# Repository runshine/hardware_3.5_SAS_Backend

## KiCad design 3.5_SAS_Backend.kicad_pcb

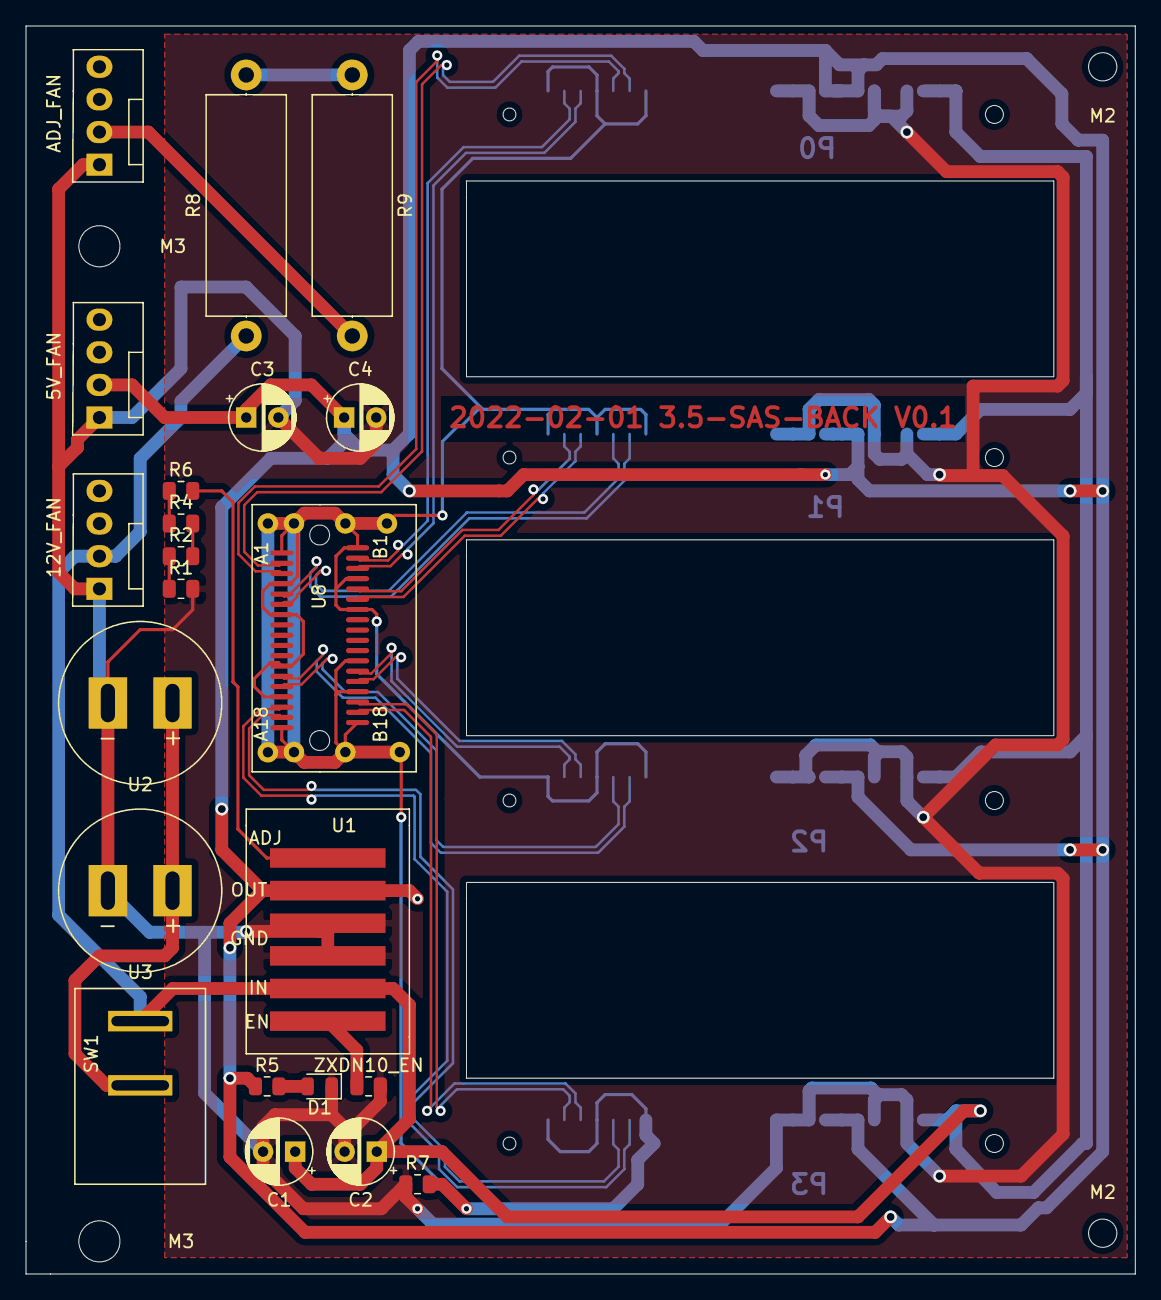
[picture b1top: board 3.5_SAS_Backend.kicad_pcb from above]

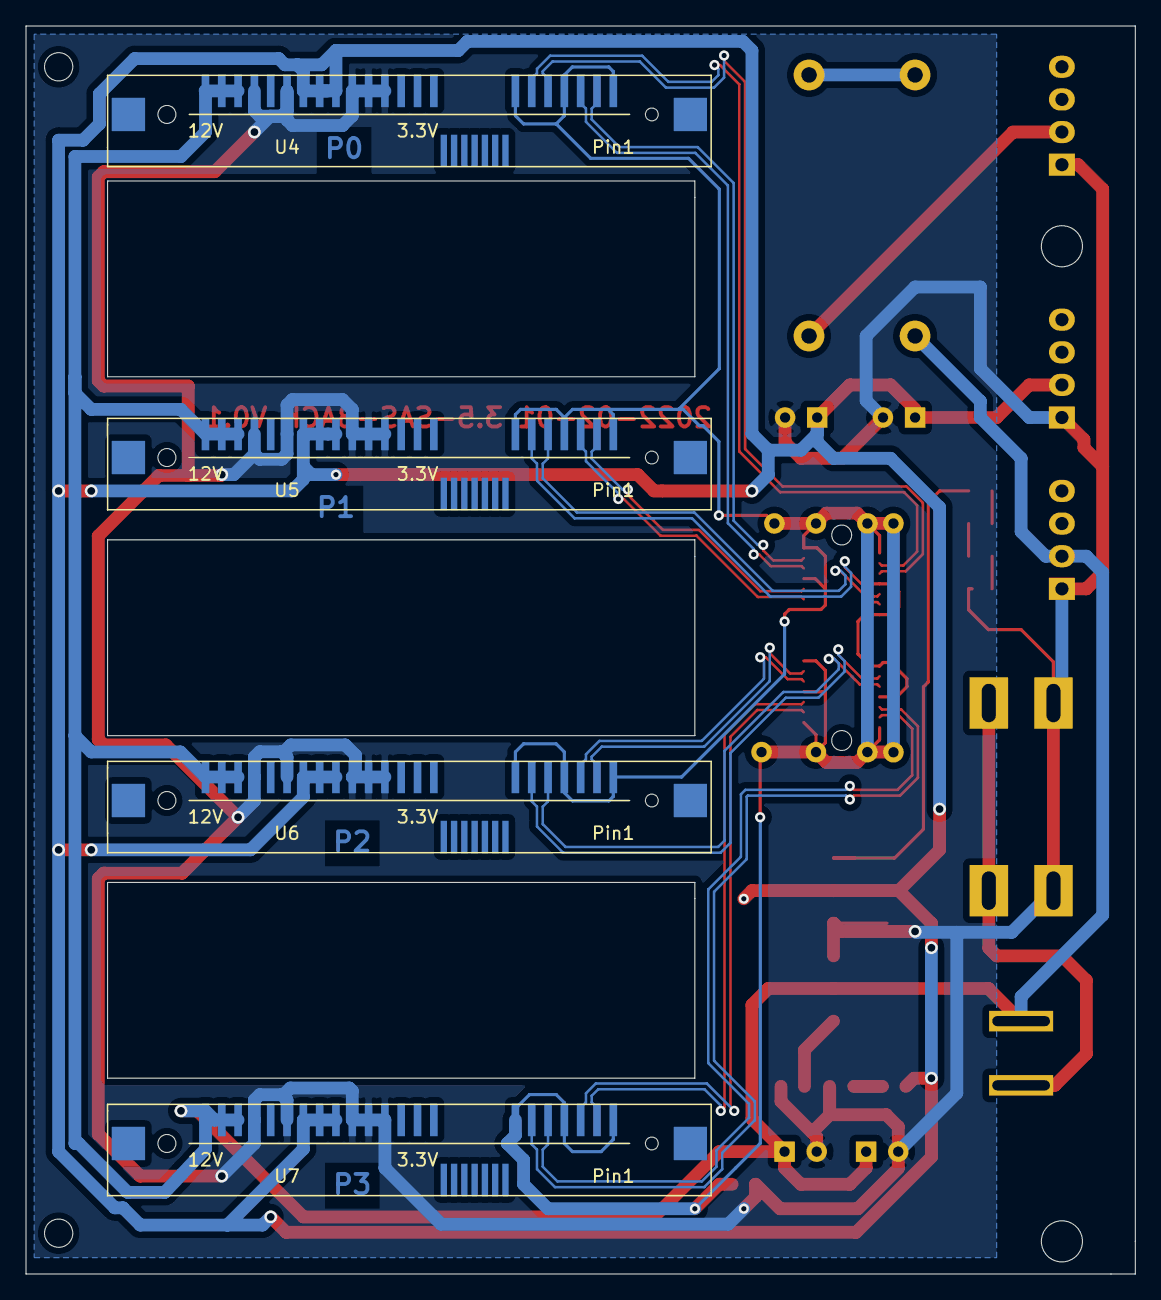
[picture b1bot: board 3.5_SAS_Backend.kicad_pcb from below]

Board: 2 copper layers, 86.4 x 97.2 mm, 30 parts (4 on the bottom side), 29 nets.

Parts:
5V_FAN: 5V_FAN; FanPinHeader_1x04_P2.54mm_Vertical
12V_FAN: 12V_FAN; FanPinHeader_1x04_P2.54mm_Vertical
ADJ_FAN: ADJ_FAN; FanPinHeader_1x04_P2.54mm_Vertical
C1, C2, C3, C4: C; CP_Radial_D5.0mm_P2.50mm
D1: LED; D_0805_2012Metric
M2, M2#2: MountingHole_2.2mm_M2
M3, M3#2: MountingHole_3.2mm_M3
R1: 2R; R_0805_2012Metric
R2, R7: 0R; R_0805_2012Metric
R4: 10R; R_0805_2012Metric
R5: 10KR; R_0805_2012Metric
R6: 100R; R_0805_2012Metric
R8, R9: ADJ_R; R_Axial_DIN0617_L17.0mm_D6.0mm_P20.32mm_Horizontal
SW1: SW_DIP_x01; SWITCH_2PIN
U1: ZXDN10_S1205SAW; ZXDN10S1205SAW
U2, U3: DC_022B_5.5*2.1_2; DC_022B_2
U4, U5, U6, U7: SAS_29; SAS_SMD_29P
U8: SFF-8087; SFF-8087-H
ZXDN10_EN: 0R; R_0805_2012Metric

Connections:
+5V: 5V_FAN.2, C3.1, C4.1, R5.1, U1.5, U4.21, U4.22, U4.23, U5.21, U5.22, U5.23, U6.21, U6.22, U6.23, U7.21, U7.22, U7.23
+12V: 12V_FAN.2, C1.1, C2.1, R8.1, SW1.1, U1.2, U4.27, U4.28, U4.29, U5.27, U5.28, U5.29, U6.27, U6.28, U6.29, U7.27, U7.28, U7.29
GND: 5V_FAN.1, 12V_FAN.1, ADJ_FAN.1, C1.2, C2.2, C3.2, C4.2, D1.1, R1.2, R7.1, U1.3, U1.4, U2.2, U3.2, U4.18, U4.19, U4.20, U4.24, U4.26, U5.18, U5.19, U5.20, U5.24, U5.26, U6.18, U6.19, U6.20, U6.24, U6.26, U7.18, U7.19, U7.20, U7.24, U7.26, ZXDN10_EN.2
GNDA: R7.2, U4.1, U4.4, U4.7, U5.1, U5.4, U5.7, U6.1, U6.4, U6.7, U7.1, U7.4, U7.7, U8.A1, U8.A4, U8.A7, U8.A12, U8.A15, U8.A18, U8.B1, U8.B4, U8.B7, U8.B12, U8.B15, U8.B18
unnamed: D1.2, R5.2
unnamed: ADJ_FAN.2, R9.2
unnamed: R1.1, R2.1
unnamed: R2.2, R4.2
unnamed: U1.1, ZXDN10_EN.1
unnamed: R4.1, R6.1
unnamed: R6.2, U1.6
unnamed: R8.2, R9.1
unnamed: SW1.2, U2.1, U3.1
P0_RXD_N: U4.5, U8.A3
P0_RXD_P: U4.6, U8.A2
P0_TXD_N: U4.3, U8.B3
P0_TXD_P: U4.2, U8.B2
P1_RXD_N: U5.5, U8.A6
P1_RXD_P: U5.6, U8.A5
P1_TXD_N: U5.3, U8.B6
P1_TXD_P: U5.2, U8.B5
P2_RXD_N: U6.5, U8.A14
P2_RXD_P: U6.6, U8.A13
P2_TXD_N: U6.3, U8.B14
P2_TXD_P: U6.2, U8.B13
P3_RXD_N: U7.5, U8.A17
P3_RXD_P: U7.6, U8.A16
P3_TXD_N: U7.3, U8.B17
P3_TXD_P: U7.2, U8.B16

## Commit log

2022-02-13 fix bugs
